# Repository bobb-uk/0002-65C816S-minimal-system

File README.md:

# 0002-65C816S minimal system
This circuit board supports a single WDC 65C816S microprocessor.
It allows attachment to a Digilent Spartan3A Starter Kit via a breakout board (see project [0001](https://github.com/bobb-uk/0001-Spartan3A-FX2-breakout))

The circuit is as basic as it can be.
Only two decoupling capacitors are used, though there are two more empty places incase of decoupling problems.

## Purpose
Purely for fun, to learn Verilog and use the Spartan3A Starter Kit will all its on-board peripherals.

## Board
4 layer FR4.  Top & Bot for signal routing.  Inner 1 & 2 provide GND and Power planes.
See [fabrication PDF](https://github.com/bobb-uk/0002-65C816S-minimal-system/blob/main/Fabrication%20data/0002-65C816S-minimal%20Fabrication%20and%20Assembly.pdf) for layer geometries, silkscreen and assembly.

BOM information, what little there is, can be found in the BOM [folder](https://github.com/bobb-uk/0002-65C816S-minimal-system/tree/main/BOM).

# WDC65C816S
Information in this enhanced version of the 6502 can be found at the [wdc65xx](https://wdc65xx.com/) and [Western Design Center](https://www.westerndesigncenter.com/) websites.

# Revisions
A : 8 June 2024 : CERN-OHL-W rev 2

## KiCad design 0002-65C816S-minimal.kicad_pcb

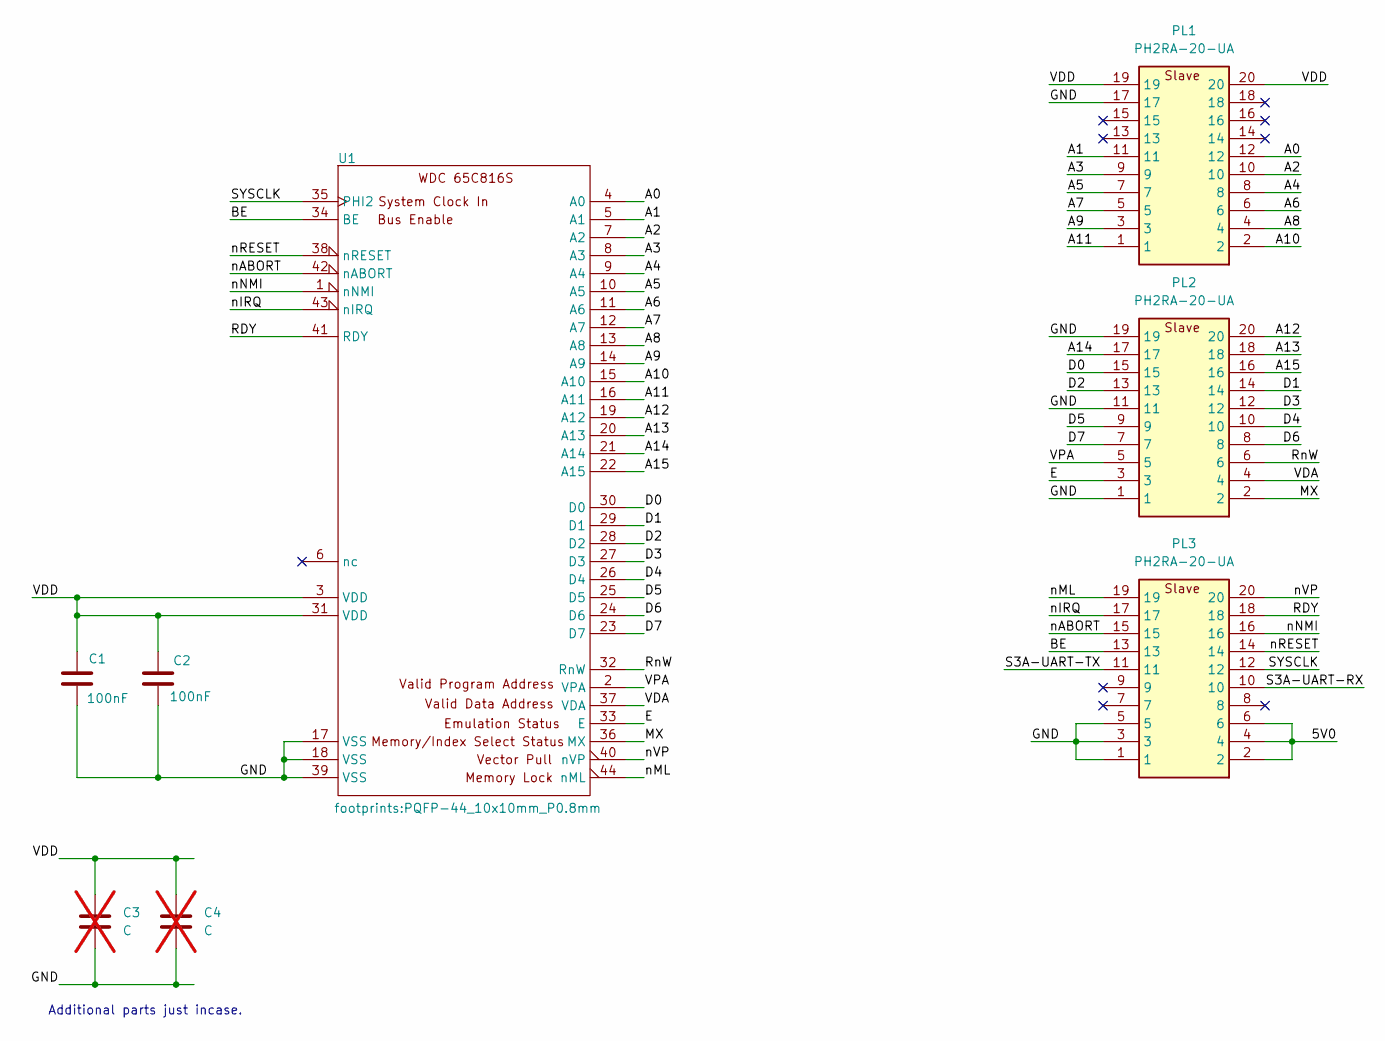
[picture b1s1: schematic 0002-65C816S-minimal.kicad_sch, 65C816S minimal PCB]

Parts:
C1, C2: 100nF; C_0603_1608Metric_Pad1.08x0.95mm_HandSolder
C3, C4: C; C_0603_1608Metric_Pad1.08x0.95mm_HandSolder; not fitted
PL1, PL2, PL3: PH2RA-20-UA; ADAM-TECH-PH2RA-20-UA; Mouser Part Number 737-PH2RA-20-UA
U1: PQFP-44_10x10mm_P0.8mm

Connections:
/5V0: PL3.2, PL3.4, PL3.6
/A0: PL1.12, U1.4 (A0)
/A1: PL1.11, U1.5 (A1)
/A2: PL1.10, U1.7 (A2)
/A3: PL1.9, U1.8 (A3)
/A4: PL1.8, U1.9 (A4)
/A5: PL1.7, U1.10 (A5)
/A6: PL1.6, U1.11 (A6)
/A7: PL1.5, U1.12 (A7)
/A8: PL1.4, U1.13 (A8)
/A9: PL1.3, U1.14 (A9)
/A10: PL1.2, U1.15 (A10)
/A11: PL1.1, U1.16 (A11)
/A12: PL2.20, U1.19 (A12)
/A13: PL2.18, U1.20 (A13)
/A14: PL2.17, U1.21 (A14)
/A15: PL2.16, U1.22 (A15)
/BE: PL3.13, U1.34 (BE)
/D0: PL2.15, U1.30 (D0)
/D1: PL2.14, U1.29 (D1)
/D2: PL2.13, U1.28 (D2)
/D3: PL2.12, U1.27 (D3)
/D4: PL2.10, U1.26 (D4)
/D5: PL2.9, U1.25 (D5)
/D6: PL2.8, U1.24 (D6)
/D7: PL2.7, U1.23 (D7)
/E: PL2.3, U1.33 (E)
/GND: C1.2, C2.2, C3.2, C4.2, PL1.17, PL2.1, PL2.11, PL2.19, PL3.1, PL3.3, PL3.5, U1.17 (VSS), U1.18 (VSS), U1.39 (VSS)
/MX: PL2.2, U1.36 (MX)
/RDY: PL3.18, U1.41 (RDY)
/RnW: PL2.6, U1.32 (RnW)
/S3A-UART-RX: PL3.10
/S3A-UART-TX: PL3.11
/SYSCLK: PL3.12, U1.35 (PHI2)
/VDA: PL2.4, U1.37 (VDA)
/VDD: C1.1, C2.1, C3.1, C4.1, PL1.19, PL1.20, U1.3 (VDD), U1.31 (VDD)
/VPA: PL2.5, U1.2 (VPA)
/nABORT: PL3.15, U1.42 (nABORT)
/nIRQ: PL3.17, U1.43 (nIRQ)
/nML: PL3.19, U1.44 (nML)
/nNMI: PL3.16, U1.1 (nNMI)
/nRESET: PL3.14, U1.38 (nRESET)
/nVP: PL3.20, U1.40 (nVP)

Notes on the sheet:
Additional parts just incase.

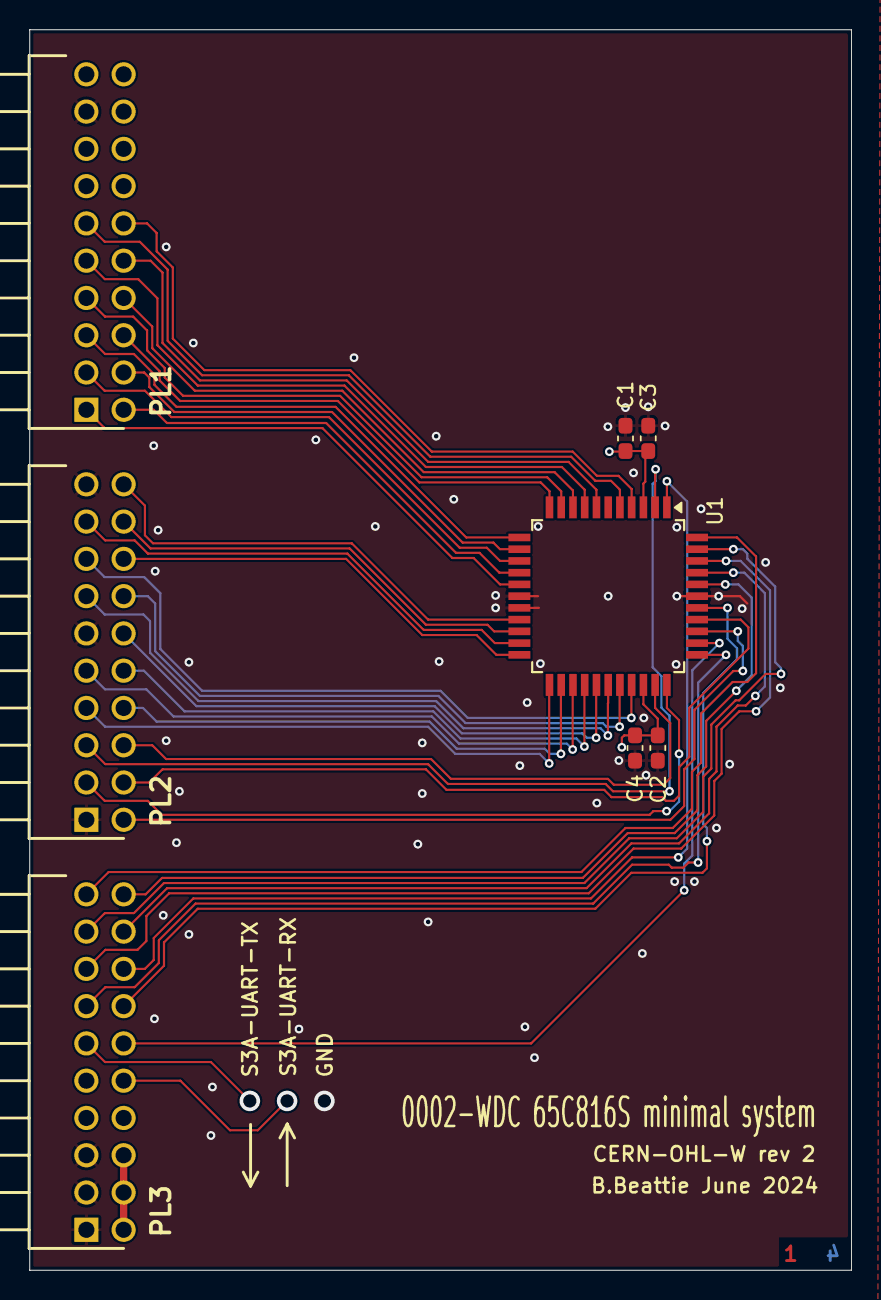
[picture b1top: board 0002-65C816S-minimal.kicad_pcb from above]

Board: 4 copper layers, 56.0 x 84.5 mm, 8 parts (0 on the bottom side), 41 nets.

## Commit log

2024-06-08 BOM pdf not on one sheet
2024-06-08 add Images/
2024-06-08 add CERN licence
2024-06-08 replace old Fab.zip file

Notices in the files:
0002-65C816S-minimal.kicad_pcb:
CERN-OHL-W ver 2
